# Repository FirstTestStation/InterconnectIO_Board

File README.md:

# FIRST STATION TEST Interconnect IO Board 600-1000-011

## Project Overview
This project involves the assembly of a custom **Interconnect IO Circuit Board (PCB)** designed to be part of the **First TestStation** project ([FTS](https://FirstTestSTation.github.io/FTS_Website/)). The primary goal of the Interconnect IO board is to provide an interface between instruments and the Unit Under Test (U.U.T).

Many resources, such as **bank relays**, **power relays**, **Digital IO** and **communication interfaces**, have been integrated into the Interconnect IO board. These resources reduce the need for external instruments and maximize the versatility of the interface, allowing for efficient testing and broader functionality.

### Design Tools
- [KiCad 7](https://www.kicad.org/download/) - Free software application used to design the PCB.
- [LibreOffice](https://www.libreoffice.org/download/download-libreoffice/) - Free Software application used to create assembly instructions and the Bill of Materials (BOM).
- [PicPick](https://picpick.app/en/) - Free application to capture and document image.

---
### Features
- **Easy Hand Assembly**: Designed with only through-hole components, making it easy to assemble by hand.
- **Socketed Active Components**: To facilitate easy replacement without unsoldering, most active components are mounted on sockets.
- **Cost-Effective Controller**: The low-cost and powerful **Raspberry Pi Pico Microcontroller** is used to interface with the user and control internal electronics.

## Assembly Instructions
   Follow the document [Assembly_Instructions](InterconnectIO_bd/pdf/InterconnectIO_Assembly_Instruction_680-1000.pdf) to complete the assembly of the board.

## Design Files
- [Gerber Files](InterconnectIO_bd/gerber_to_order/) – Gerber files for PCB fabrication, send zip file to manufacturer (JLCPCB is the one used by the project).
- [Assembly Schematic](InterconnectIO_bd/pdf/InterconnectIO_Assembly_diagram_670-1000.pdf) – Parts and value to help hand assemblies of components.
- [Electrical Schematic](InterconnectIO_bd/pdf/interconnectIO_schematic_640-1000.pdf) – Review the full electrical schematic diagram for reference.
- [Bill of Materials (BOM)](InterconnectIO_bd/pdf/BOM_InterconnectIO_Board_610-1000.pdf) – List of components required for assembly.

---

## License

This project is licensed under the terms of the [CERN Open Hardware License Version 2 - Weakly Reciprocal (CERN-OHL-W 2.0)](https://ohwr.org/cern_ohl_w_v2.txt).

See the [LICENSE](./LICENSE) file in this repository for more details.

---

## History
- **Version 1.0**: The initial version of the PCB (600-1010-010) has been assembled and tested. Wiring errors on the UART were identified and corrected manually using wires.
- **Version 1.1**: This version addresses all errors identified in Version 1.0. As of now, Version 1.1 has not yet been assembled or tested.
---

## Contact
For any issues or further questions, feel free to contact me at [daniellockhead@gmail.com] or open an issue on GitHub.

---

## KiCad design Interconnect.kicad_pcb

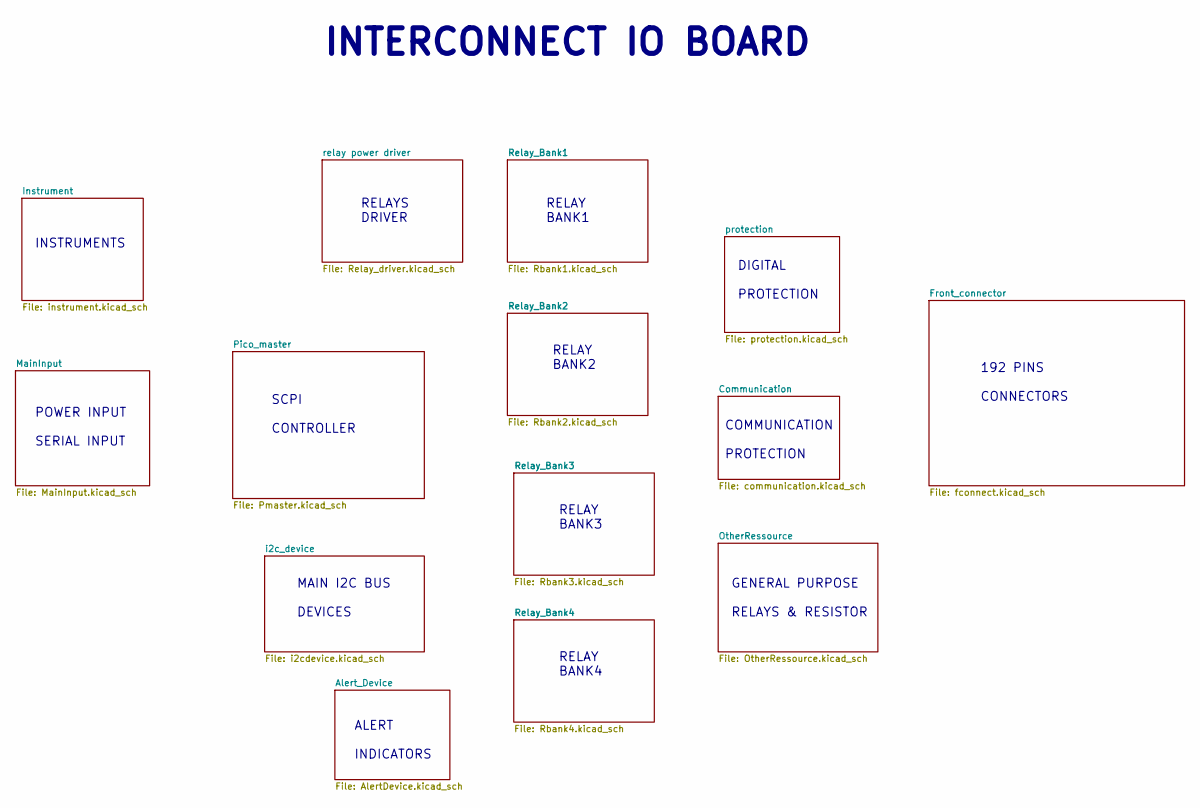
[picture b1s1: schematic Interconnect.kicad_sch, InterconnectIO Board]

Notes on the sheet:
ALERT INDICATORS
COMMUNICATION PROTECTION
SCPI CONTROLLER
RELAY BANK3
RELAYS DRIVER
INTERCONNECT IO BOARD
INSTRUMENTS
DIGITAL PROTECTION
GENERAL PURPOSE RELAYS & RESISTOR
192 PINS CONNECTORS
MAIN I2C BUS DEVICES
RELAY BANK2
RELAY BANK1
POWER INPUT SERIAL INPUT
RELAY BANK4

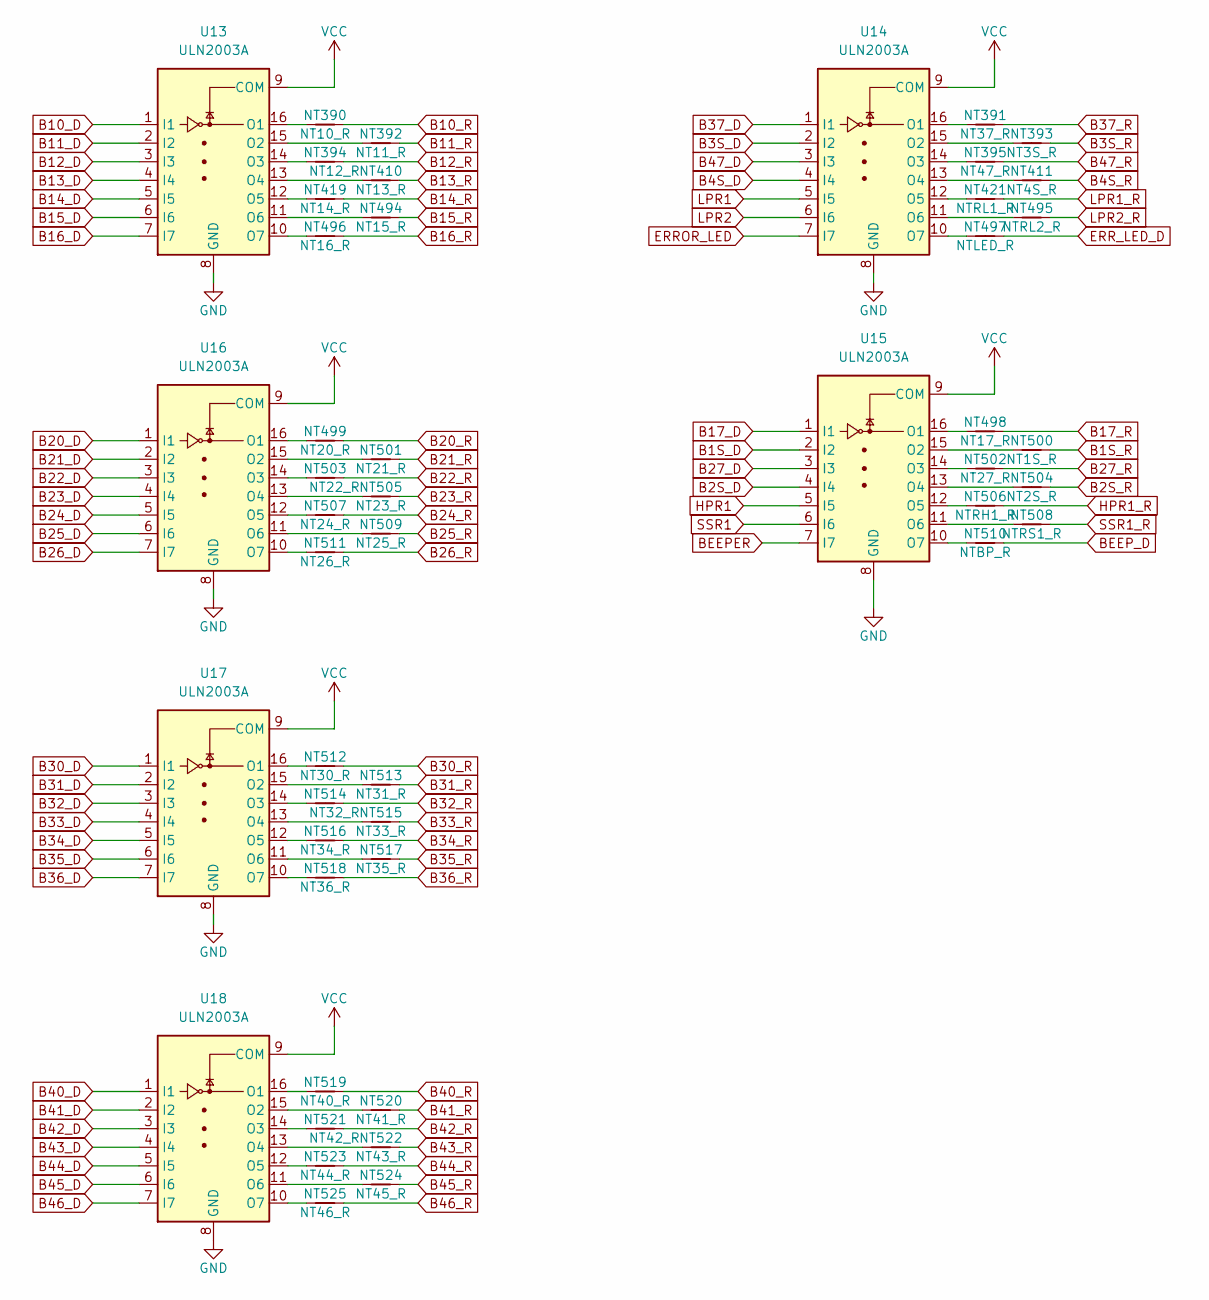
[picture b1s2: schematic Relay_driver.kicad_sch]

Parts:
NT390: NT10_R; NetTie-2_Front1.0mm
NT391: NT37_R; NetTie-2_Front1.0mm
NT392: NT11_R; NetTie-2_Front1.0mm
NT393: NT3S_R; NetTie-2_Front1.0mm
NT394: NT12_R; NetTie-2_Front1.0mm
NT395: NT47_R; NetTie-2_Front1.0mm
NT410: NT13_R; NetTie-2_Front1.0mm
NT411: NT4S_R; NetTie-2_Front1.0mm
NT419: NT14_R; NetTie-2_Front1.0mm
NT421: NTRL1_R; NetTie-2_Front1.0mm
NT494: NT15_R; NetTie-2_Front1.0mm
NT495: NTRL2_R; NetTie-2_Front1.0mm
NT496: NT16_R; NetTie-2_Front1.0mm
NT497: NTLED_R; NetTie-2_Front1.0mm
NT498: NT17_R; NetTie-2_Front1.0mm
NT499: NT20_R; NetTie-2_Front1.0mm
NT500: NT1S_R; NetTie-2_Front1.0mm
NT501: NT21_R; NetTie-2_Front1.0mm
NT502: NT27_R; NetTie-2_Front1.0mm
NT503: NT22_R; NetTie-2_Front1.0mm
NT504: NT2S_R; NetTie-2_Front1.0mm
NT505: NT23_R; NetTie-2_Front1.0mm
NT506: NTRH1_R; NetTie-2_Front1.0mm
NT507: NT24_R; NetTie-2_Front1.0mm
NT508: NTRS1_R; NetTie-2_Front1.0mm
NT509: NT25_R; NetTie-2_Front1.0mm
NT510: NTBP_R; NetTie-2_Front1.0mm
NT511: NT26_R; NetTie-2_Front1.0mm
NT512: NT30_R; NetTie-2_Front1.0mm
NT513: NT31_R; NetTie-2_Front1.0mm
NT514: NT32_R; NetTie-2_Front1.0mm
NT515: NT33_R; NetTie-2_Front1.0mm
NT516: NT34_R; NetTie-2_Front1.0mm
NT517: NT35_R; NetTie-2_Front1.0mm
NT518: NT36_R; NetTie-2_Front1.0mm
NT519: NT40_R; NetTie-2_Front1.0mm
NT520: NT41_R; NetTie-2_Front1.0mm
NT521: NT42_R; NetTie-2_Front1.0mm
NT522: NT43_R; NetTie-2_Front1.0mm
NT523: NT44_R; NetTie-2_Front1.0mm
NT524: NT45_R; NetTie-2_Front1.0mm
NT525: NT46_R; NetTie-2_Front1.0mm
U13, U14, U15, U16, U17, U18: ULN2003A; DIP-16_W7.62mm_LongPads

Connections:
B1S_D: U15.2 (I2); also elsewhere on the board
B1S_R: NT500.2; also elsewhere on the board
B2S_D: U15.4 (I4); also elsewhere on the board
B2S_R: NT504.2; also elsewhere on the board
B3S_D: U14.2 (I2); also elsewhere on the board
B3S_R: NT393.2; also elsewhere on the board
B4S_D: U14.4 (I4); also elsewhere on the board
B4S_R: NT411.2; also elsewhere on the board
B10_D: U13.1 (I1); also elsewhere on the board
B10_R: NT390.2; also elsewhere on the board
B11_D: U13.2 (I2); also elsewhere on the board
B11_R: NT392.2
B12_D: U13.3 (I3); also elsewhere on the board
B12_R: NT394.2; also elsewhere on the board
B13_D: U13.4 (I4); also elsewhere on the board
B13_R: NT410.2; also elsewhere on the board
B14_D: U13.5 (I5); also elsewhere on the board
B14_R: NT419.2; also elsewhere on the board
B15_D: U13.6 (I6); also elsewhere on the board
B15_R: NT494.2; also elsewhere on the board
B16_D: U13.7 (I7); also elsewhere on the board
B16_R: NT496.2; also elsewhere on the board
B17_D: U15.1 (I1); also elsewhere on the board
B17_R: NT498.2; also elsewhere on the board
B20_D: U16.1 (I1); also elsewhere on the board
B20_R: NT499.2; also elsewhere on the board
B21_D: U16.2 (I2); also elsewhere on the board
B21_R: NT501.2; also elsewhere on the board
B22_D: U16.3 (I3); also elsewhere on the board
B22_R: NT503.2; also elsewhere on the board
B23_D: U16.4 (I4); also elsewhere on the board
B23_R: NT505.2; also elsewhere on the board
B24_D: U16.5 (I5); also elsewhere on the board
B24_R: NT507.2; also elsewhere on the board
B25_D: U16.6 (I6); also elsewhere on the board
B25_R: NT509.2; also elsewhere on the board
B26_D: U16.7 (I7); also elsewhere on the board
B26_R: NT511.2; also elsewhere on the board
B27_D: U15.3 (I3); also elsewhere on the board
B27_R: NT502.2; also elsewhere on the board
B30_D: U17.1 (I1); also elsewhere on the board
B30_R: NT512.2; also elsewhere on the board
B31_D: U17.2 (I2); also elsewhere on the board
B31_R: NT513.2
B32_D: U17.3 (I3); also elsewhere on the board
B32_R: NT514.2; also elsewhere on the board
B33_D: U17.4 (I4); also elsewhere on the board
B33_R: NT515.2; also elsewhere on the board
B34_D: U17.5 (I5); also elsewhere on the board
B34_R: NT516.2; also elsewhere on the board
B35_D: U17.6 (I6); also elsewhere on the board
B35_R: NT517.2; also elsewhere on the board
B36_D: U17.7 (I7); also elsewhere on the board
B36_R: NT518.2; also elsewhere on the board
B37_D: U14.1 (I1); also elsewhere on the board
B37_R: NT391.2; also elsewhere on the board
B40_D: U18.1 (I1); also elsewhere on the board
B40_R: NT519.2; also elsewhere on the board
B41_D: U18.2 (I2); also elsewhere on the board
B41_R: NT520.2; also elsewhere on the board
B42_D: U18.3 (I3); also elsewhere on the board
B42_R: NT521.2; also elsewhere on the board
B43_D: U18.4 (I4); also elsewhere on the board
B43_R: NT522.2; also elsewhere on the board
B44_D: U18.5 (I5); also elsewhere on the board
B44_R: NT523.2; also elsewhere on the board
B45_D: U18.6 (I6); also elsewhere on the board
B45_R: NT524.2; also elsewhere on the board
B46_D: U18.7 (I7); also elsewhere on the board
B46_R: NT525.2; also elsewhere on the board
B47_D: U14.3 (I3); also elsewhere on the board
B47_R: NT395.2; also elsewhere on the board
BEEPER: U15.7 (I7); also elsewhere on the board
BEEP_D: NT510.2; also elsewhere on the board
ERROR_LED: U14.7 (I7); also elsewhere on the board
ERR_LED_D: NT497.2
GND: U13.8 (GND), U14.8 (GND), U15.8 (GND), U16.8 (GND), U17.8 (GND), U18.8 (GND); also elsewhere on the board
HPR1: U15.5 (I5); also elsewhere on the board
HPR1_R: NT506.2; also elsewhere on the board
LPR1: U14.5 (I5); also elsewhere on the board
LPR1_R: NT421.2; also elsewhere on the board
LPR2: U14.6 (I6); also elsewhere on the board
LPR2_R: NT495.2; also elsewhere on the board
unnamed: NT390.1, U13.16 (O1)
unnamed: NT391.1, U14.16 (O1)
unnamed: NT392.1, U13.15 (O2)
unnamed: NT393.1, U14.15 (O2)
unnamed: NT394.1, U13.14 (O3)
unnamed: NT395.1, U14.14 (O3)
unnamed: NT410.1, U13.13 (O4)
unnamed: NT411.1, U14.13 (O4)
unnamed: NT419.1, U13.12 (O5)
unnamed: NT421.1, U14.12 (O5)
unnamed: NT494.1, U13.11 (O6)
unnamed: NT495.1, U14.11 (O6)
unnamed: NT496.1, U13.10 (O7)
unnamed: NT497.1, U14.10 (O7)
unnamed: NT498.1, U15.16 (O1)
unnamed: NT499.1, U16.16 (O1)
unnamed: NT500.1, U15.15 (O2)
unnamed: NT501.1, U16.15 (O2)
unnamed: NT502.1, U15.14 (O3)
unnamed: NT503.1, U16.14 (O3)
unnamed: NT504.1, U15.13 (O4)
unnamed: NT505.1, U16.13 (O4)
unnamed: NT506.1, U15.12 (O5)
unnamed: NT507.1, U16.12 (O5)
unnamed: NT508.1, U15.11 (O6)
unnamed: NT509.1, U16.11 (O6)
unnamed: NT510.1, U15.10 (O7)
unnamed: NT511.1, U16.10 (O7)
unnamed: NT512.1, U17.16 (O1)
unnamed: NT513.1, U17.15 (O2)
unnamed: NT514.1, U17.14 (O3)
unnamed: NT515.1, U17.13 (O4)
unnamed: NT516.1, U17.12 (O5)
unnamed: NT517.1, U17.11 (O6)
unnamed: NT518.1, U17.10 (O7)
unnamed: NT519.1, U18.16 (O1)
unnamed: NT520.1, U18.15 (O2)
unnamed: NT521.1, U18.14 (O3)
unnamed: NT522.1, U18.13 (O4)
unnamed: NT523.1, U18.12 (O5)
unnamed: NT524.1, U18.11 (O6)
unnamed: NT525.1, U18.10 (O7)
PWR_5V: U13.9 (COM), U14.9 (COM), U15.9 (COM), U16.9 (COM), U17.9 (COM), U18.9 (COM); also elsewhere on the board
SSR1: U15.6 (I6); also elsewhere on the board
SSR1_R: NT508.2; also elsewhere on the board

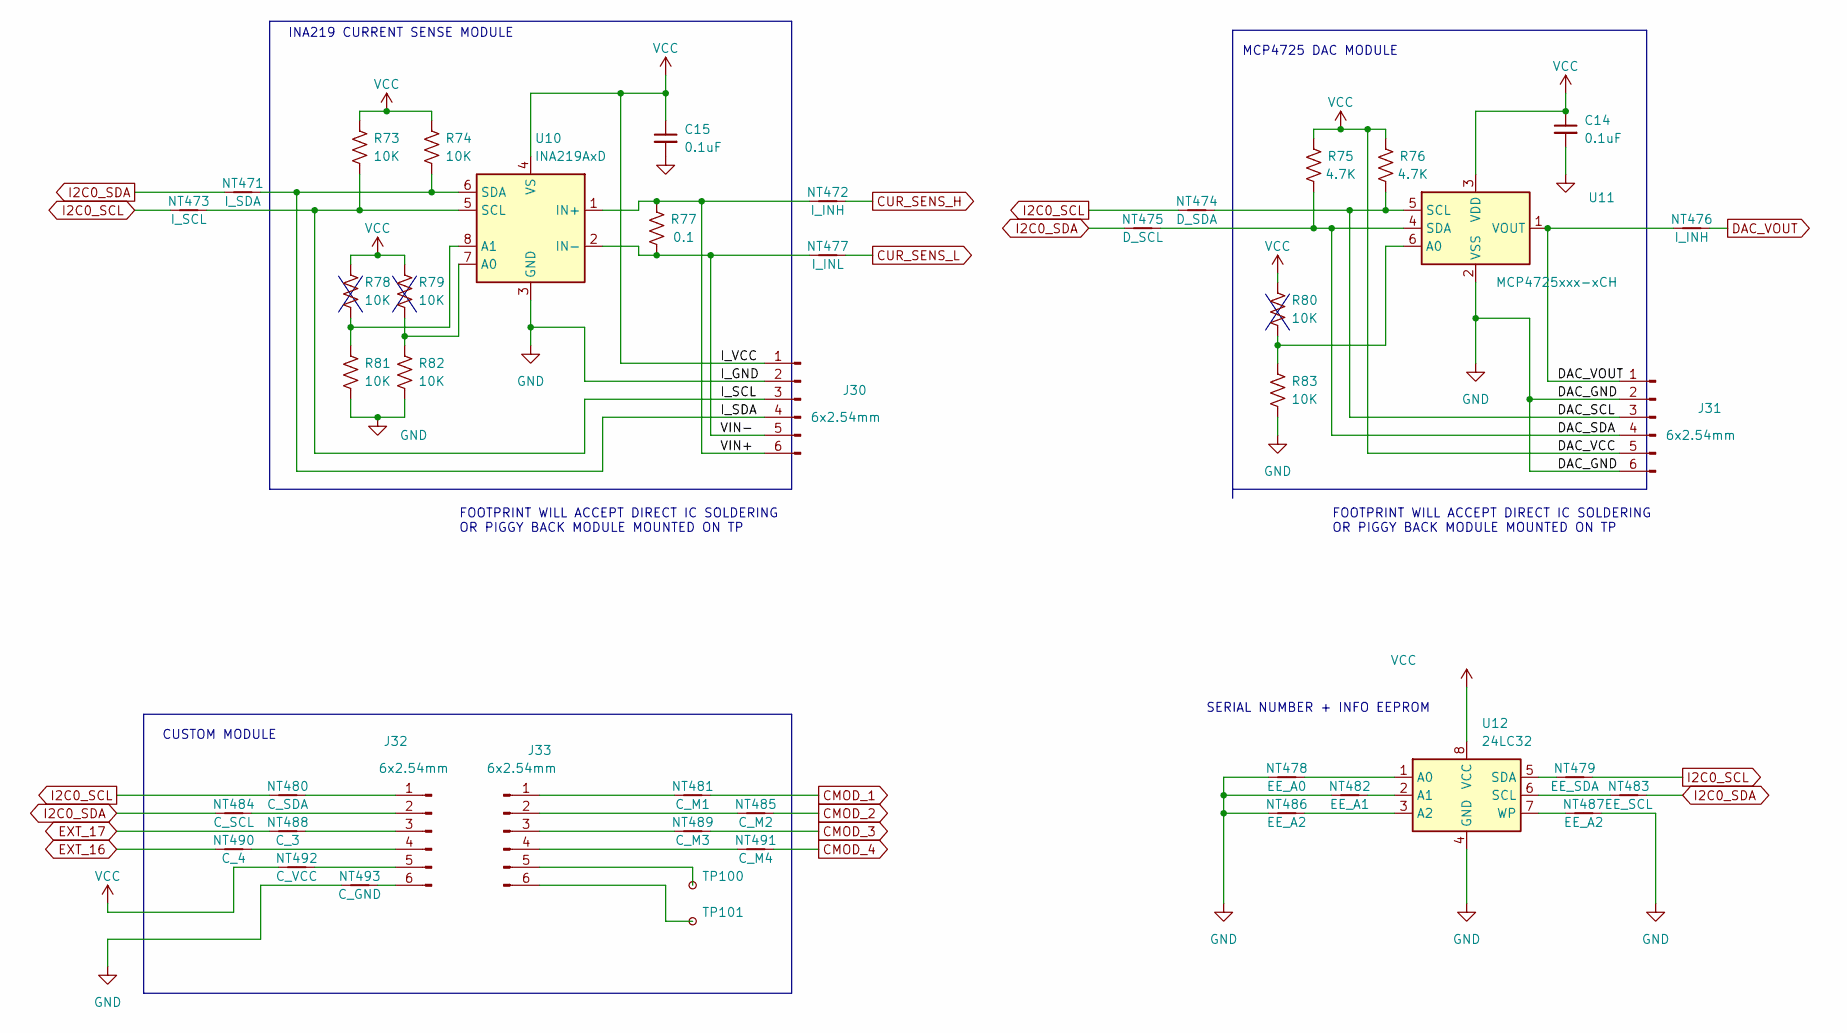
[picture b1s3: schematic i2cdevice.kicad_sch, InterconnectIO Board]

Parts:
C14: 0.1uF; C_0603_1608Metric_Pad1.08x0.95mm_HandSolder
C15: 0.1uF; C_0805_2012Metric_Pad1.18x1.45mm_HandSolder
J30, J31, J32, J33: 6x2.54mm; PinHeader_1x06_P2.54mm_Vertical
NT471: I_SDA; NetTie-2_Front1.0mm
NT472, NT476: I_INH; NetTie-2_Front1.0mm
NT473: I_SCL; NetTie-2_Front1.0mm
NT474: D_SDA; NetTie-2_Front1.0mm
NT475: D_SCL; NetTie-2_Front1.0mm
NT477: I_INL; NetTie-2_Front1.0mm
NT478: EE_A0; NetTie-2_Front1.0mm
NT479: EE_SDA; NetTie-2_Front1.0mm
NT480: C_SDA; NetTie-2_Front1.0mm
NT481: C_M1; NetTie-2_Front1.0mm
NT482: EE_A1; NetTie-2_Front1.0mm
NT483: EE_SCL; NetTie-2_Front1.0mm
NT484: C_SCL; NetTie-2_Front1.0mm
NT485: C_M2; NetTie-2_Front1.0mm
NT486, NT487: EE_A2; NetTie-2_Front1.0mm
NT488: C_3; NetTie-2_Front1.0mm
NT489: C_M3; NetTie-2_Front1.0mm
NT490: C_4; NetTie-2_Front1.0mm
NT491: C_M4; NetTie-2_Front1.0mm
NT492: C_VCC; NetTie-2_Front1.0mm
NT493: C_GND; NetTie-2_Front1.0mm
R73, R74, R78, R79, R80, R81, R82: 10K; R_0805_2012Metric_Pad1.20x1.40mm_HandSolder
R75, R76: 4.7K; R_0603_1608Metric_Pad0.98x0.95mm_HandSolder
R77: 0.1; R_2512_6332Metric_Pad1.40x3.35mm_HandSolder
R83: 10K; R_0603_1608Metric_Pad0.98x0.95mm_HandSolder
TP100, TP101: TestPoint_Small; Pin_D0.9mm_L10.0mm_W2.4mm_FlatFork
U10: INA219AxD; SOT-23-8
U11: MCP4725xxx-xCH; SOT-23-6
U12: 24LC32; DIP-8_W7.62mm

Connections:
/i2c_device/DAC_SCL: J31.3, NT474.2, R76.1, U11.5 (SCL)
/i2c_device/DAC_SDA: J31.4, NT475.2, R75.1, U11.4 (SDA)
/i2c_device/I_SCL: J30.3, NT473.2, R73.1, U10.5 (SCL)
/i2c_device/I_SDA: J30.4, NT471.2, R74.1, U10.6 (SDA)
/i2c_device/VIN+: J30.6, NT472.2, R77.2, U10.1 (IN+)
/i2c_device/VIN-: J30.5, NT477.2, R77.1, U10.2 (IN-)
CMOD_1: NT481.2; also elsewhere on the board
CMOD_2: NT485.2; also elsewhere on the board
CMOD_3: NT489.2; also elsewhere on the board
CMOD_4: NT491.2; also elsewhere on the board
CUR_SENS_H: NT472.1; also elsewhere on the board
CUR_SENS_L: NT477.1; also elsewhere on the board
DAC_VOUT: J31.1, NT476.1, NT476.2, U11.1 (VOUT); also elsewhere on the board
EXT_16: NT490.1; also elsewhere on the board
EXT_17: NT488.1; also elsewhere on the board
GND: C14.2, C15.2, J30.2, J31.2, J31.6, NT478.1, NT482.1, NT486.1, NT487.1, NT493.1, R81.1, R82.1, R83.1, U10.3 (GND), U11.2 (VSS), U12.4 (GND); also elsewhere on the board
I2C0_SCL: NT473.1, NT474.1, NT479.1, NT480.1; also elsewhere on the board
I2C0_SDA: NT471.1, NT475.1, NT483.1, NT484.1; also elsewhere on the board
unnamed: J32.1, NT480.2
unnamed: J32.2, NT484.2
unnamed: J32.3, NT488.2
unnamed: J32.4, NT490.2
unnamed: J32.5, NT492.2
unnamed: J32.6, NT493.2
unnamed: J33.1, NT481.1
unnamed: J33.2, NT485.1
unnamed: J33.3, NT489.1
unnamed: J33.4, NT491.1
unnamed: J33.5, TP100.1
unnamed: J33.6, TP101.1
unnamed: NT478.2, U12.1 (A0)
unnamed: NT479.2, U12.5 (SDA)
unnamed: NT482.2, U12.2 (A1)
unnamed: NT483.2, U12.6 (SCL)
unnamed: NT486.2, U12.3 (A2)
unnamed: NT487.2, U12.7 (WP)
unnamed: R78.1, R81.2, U10.8 (A1)
unnamed: R79.1, R82.2, U10.7 (A0)
unnamed: R80.1, R83.2, U11.6 (A0)
PWR_5V: C14.1, C15.1, J30.1, J31.5, NT492.1, R73.2, R74.2, R75.2, R76.2, R78.2, R79.2, R80.2, U10.4 (VS), U11.3 (VDD), U12.8 (VCC); also elsewhere on the board

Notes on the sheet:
INA219 CURRENT SENSE MODULE
FOOTPRINT WILL ACCEPT DIRECT IC SOLDERING OR PIGGY BACK MODULE MOUNTED ON TP
MCP4725 DAC MODULE
CUSTOM MODULE
SERIAL NUMBER + INFO EEPROM

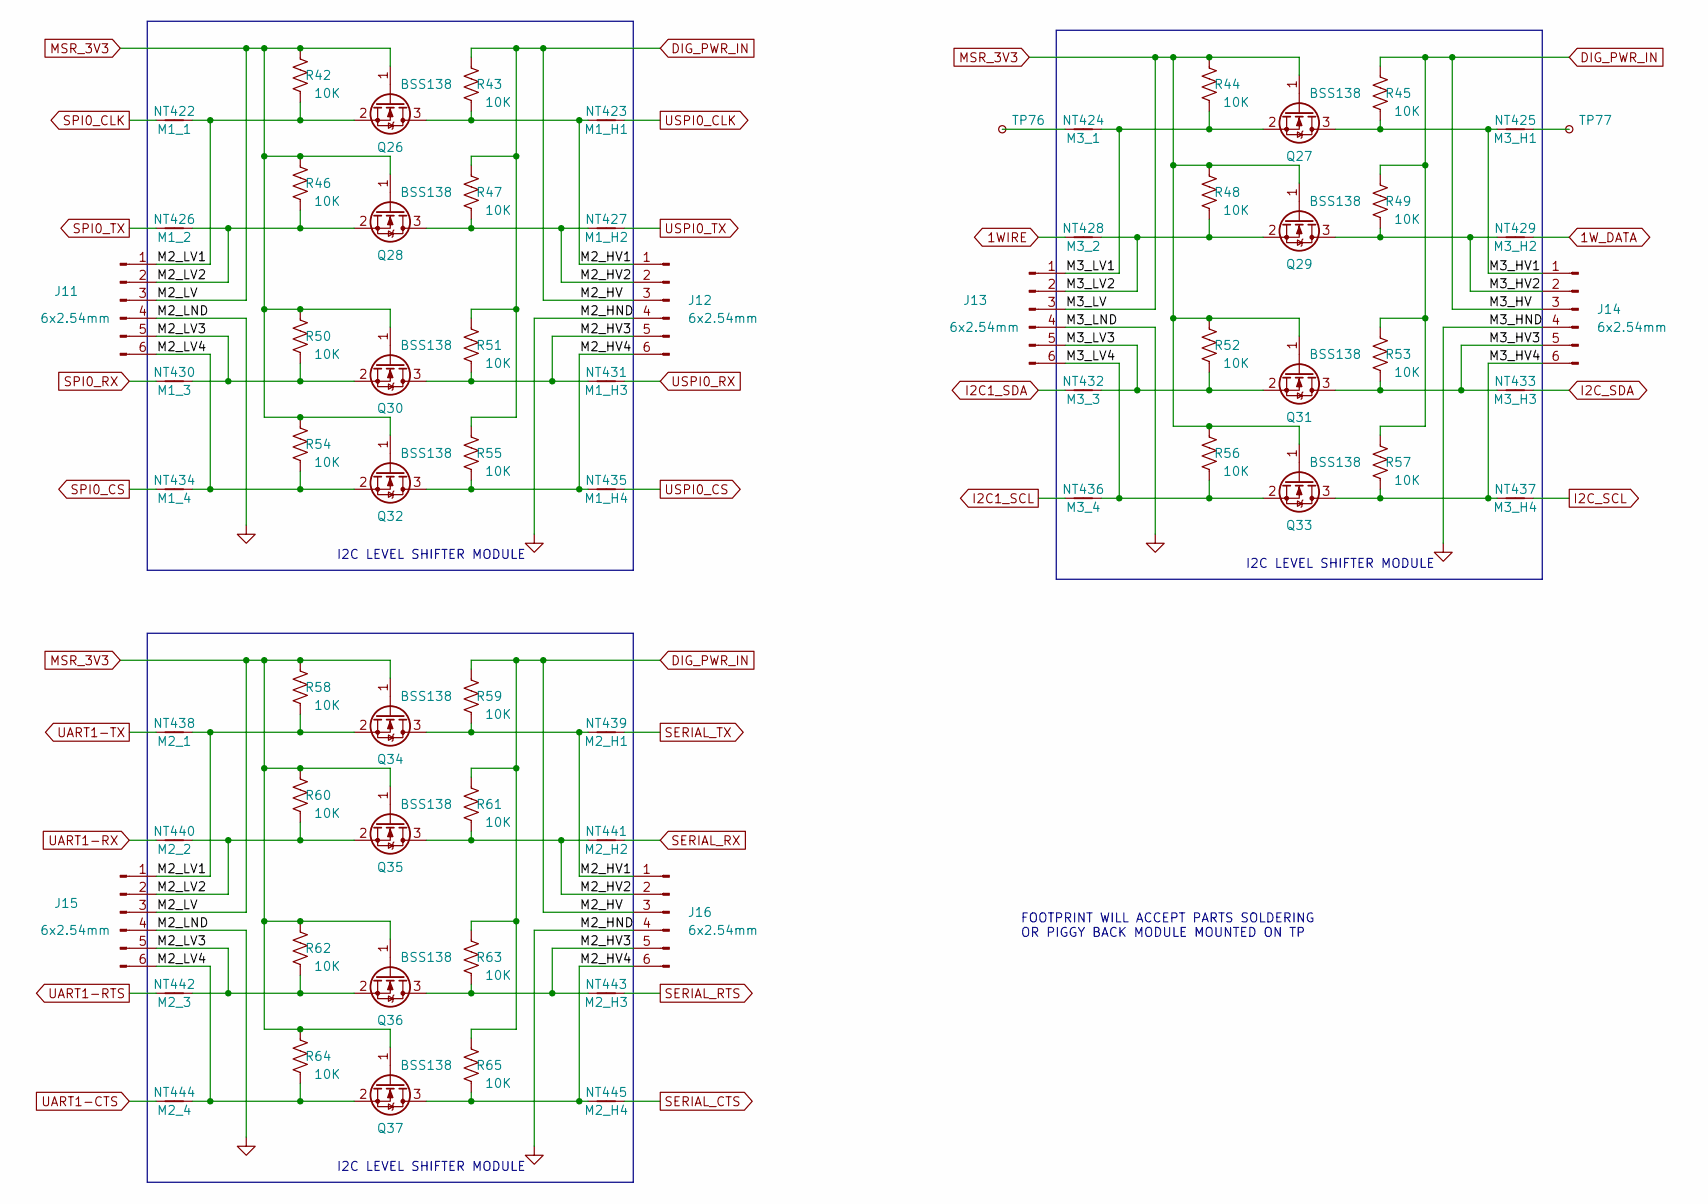
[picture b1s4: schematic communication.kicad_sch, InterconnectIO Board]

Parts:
J11, J12, J13, J14, J15, J16: 6x2.54mm; PinHeader_1x06_P2.54mm_Vertical
NT422: M1_1; NetTie-2_Front1.0mm
NT423: M1_H1; NetTie-2_Front1.0mm
NT424: M3_1; NetTie-2_Front1.0mm
NT425: M3_H1; NetTie-2_Front1.0mm
NT426: M1_2; NetTie-2_Front1.0mm
NT427: M1_H2; NetTie-2_Front1.0mm
NT428: M3_2; NetTie-2_Front1.0mm
NT429: M3_H2; NetTie-2_Front1.0mm
NT430: M1_3; NetTie-2_Front1.0mm
NT431: M1_H3; NetTie-2_Front1.0mm
NT432: M3_3; NetTie-2_Front1.0mm
NT433: M3_H3; NetTie-2_Front1.0mm
NT434: M1_4; NetTie-2_Front1.0mm
NT435: M1_H4; NetTie-2_Front1.0mm
NT436: M3_4; NetTie-2_Front1.0mm
NT437: M3_H4; NetTie-2_Front1.0mm
NT438: M2_1; NetTie-2_Front1.0mm
NT439: M2_H1; NetTie-2_Front1.0mm
NT440: M2_2; NetTie-2_Front1.0mm
NT441: M2_H2; NetTie-2_Front1.0mm
NT442: M2_3; NetTie-2_Front1.0mm
NT443: M2_H3; NetTie-2_Front1.0mm
NT444: M2_4; NetTie-2_Front1.0mm
NT445: M2_H4; NetTie-2_Front1.0mm
Q26, Q27, Q28, Q29, Q30, Q31, Q32, Q33, Q34, Q35, Q36, Q37: BSS138; SOT-23W
R42, R43, R44, R45, R46, R47, R48, R49, R50, R51, R52, R53, R54, R55, R56, R57, R58, R59, R60, R61, R62, R63, R64, R65: 10K; R_0603_1608Metric
TP76, TP77: TestPoint_Small; Pin_D0.9mm_L10.0mm_W2.4mm_FlatFork

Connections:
1WIRE: NT428.1; also elsewhere on the board
1W_DATA: NT429.1; also elsewhere on the board
/Communication/M2_HV1: J12.1, J16.1, NT423.2, NT439.2, Q26.3 (D), Q34.3 (D), R43.1, R59.1
/Communication/M2_HV2: J12.2, J16.2, NT427.2, NT441.2, Q28.3 (D), Q35.3 (D), R47.1, R61.1
/Communication/M2_HV3: J12.5, J16.5, NT431.2, NT443.2, Q30.3 (D), Q36.3 (D), R51.1, R63.1
/Communication/M2_HV4: J12.6, J16.6, NT435.2, NT445.2, Q32.3 (D), Q37.3 (D), R55.1, R65.1
/Communication/M2_LV1: J11.1, J15.1, NT422.2, NT438.2, Q26.2 (S), Q34.2 (S), R42.1, R58.1
/Communication/M2_LV2: J11.2, J15.2, NT426.2, NT440.2, Q28.2 (S), Q35.2 (S), R46.1, R60.1
/Communication/M2_LV3: J11.5, J15.5, NT430.2, NT442.2, Q30.2 (S), Q36.2 (S), R50.1, R62.1
/Communication/M2_LV4: J11.6, J15.6, NT434.2, NT444.2, Q32.2 (S), Q37.2 (S), R54.1, R64.1
/Communication/M3_HV1: J14.1, NT425.2, Q27.3 (D), R45.1
/Communication/M3_HV2: J14.2, NT429.2, Q29.3 (D), R49.1
/Communication/M3_HV3: J14.5, NT433.2, Q31.3 (D), R53.1
/Communication/M3_HV4: J14.6, NT437.2, Q33.3 (D), R57.1
/Communication/M3_LV1: J13.1, NT424.2, Q27.2 (S), R44.1
/Communication/M3_LV2: J13.2, NT428.2, Q29.2 (S), R48.1
/Communication/M3_LV3: J13.5, NT432.2, Q31.2 (S), R52.1
/Communication/M3_LV4: J13.6, NT436.2, Q33.2 (S), R56.1
DIG_PWR_IN: J12.3, J14.3, J16.3, R43.2, R45.2, R47.2, R49.2, R51.2, R53.2, R55.2, R57.2, R59.2, R61.2, R63.2, R65.2; also elsewhere on the board
GND: J11.4, J12.4, J13.4, J14.4, J15.4, J16.4; also elsewhere on the board
I2C1_SCL: NT436.1; also elsewhere on the board
I2C1_SDA: NT432.1; also elsewhere on the board
I2C_SCL: NT437.1; also elsewhere on the board
I2C_SDA: NT433.1; also elsewhere on the board
MSR_3V3: J11.3, J13.3, J15.3, Q26.1 (G), Q27.1 (G), Q28.1 (G), Q29.1 (G), Q30.1 (G), Q31.1 (G), Q32.1 (G), Q33.1 (G), Q34.1 (G), Q35.1 (G), Q36.1 (G), Q37.1 (G), R42.2, R44.2, R46.2, R48.2, R50.2, R52.2, R54.2, R56.2, R58.2, R60.2, R62.2, R64.2; also elsewhere on the board
unnamed: NT424.1, TP76.1
unnamed: NT425.1, TP77.1
SERIAL_CTS: NT445.1; also elsewhere on the board
SERIAL_RTS: NT443.1; also elsewhere on the board
SERIAL_RX: NT441.1; also elsewhere on the board
SERIAL_TX: NT439.1; also elsewhere on the board
SPI0_CLK: NT422.1; also elsewhere on the board
SPI0_CS: NT434.1; also elsewhere on the board
SPI0_RX: NT430.1; also elsewhere on the board
SPI0_TX: NT426.1; also elsewhere on the board
UART1-CTS: NT444.1; also elsewhere on the board
UART1-RTS: NT442.1; also elsewhere on the board
UART1-RX: NT440.1; also elsewhere on the board
UART1-TX: NT438.1; also elsewhere on the board
USPI0_CLK: NT423.1; also elsewhere on the board
USPI0_CS: NT435.1; also elsewhere on the board
USPI0_RX: NT431.1; also elsewhere on the board
USPI0_TX: NT427.1; also elsewhere on the board

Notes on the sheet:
FOOTPRINT WILL ACCEPT PARTS SOLDERING OR PIGGY BACK MODULE MOUNTED ON TP
I2C LEVEL SHIFTER MODULE

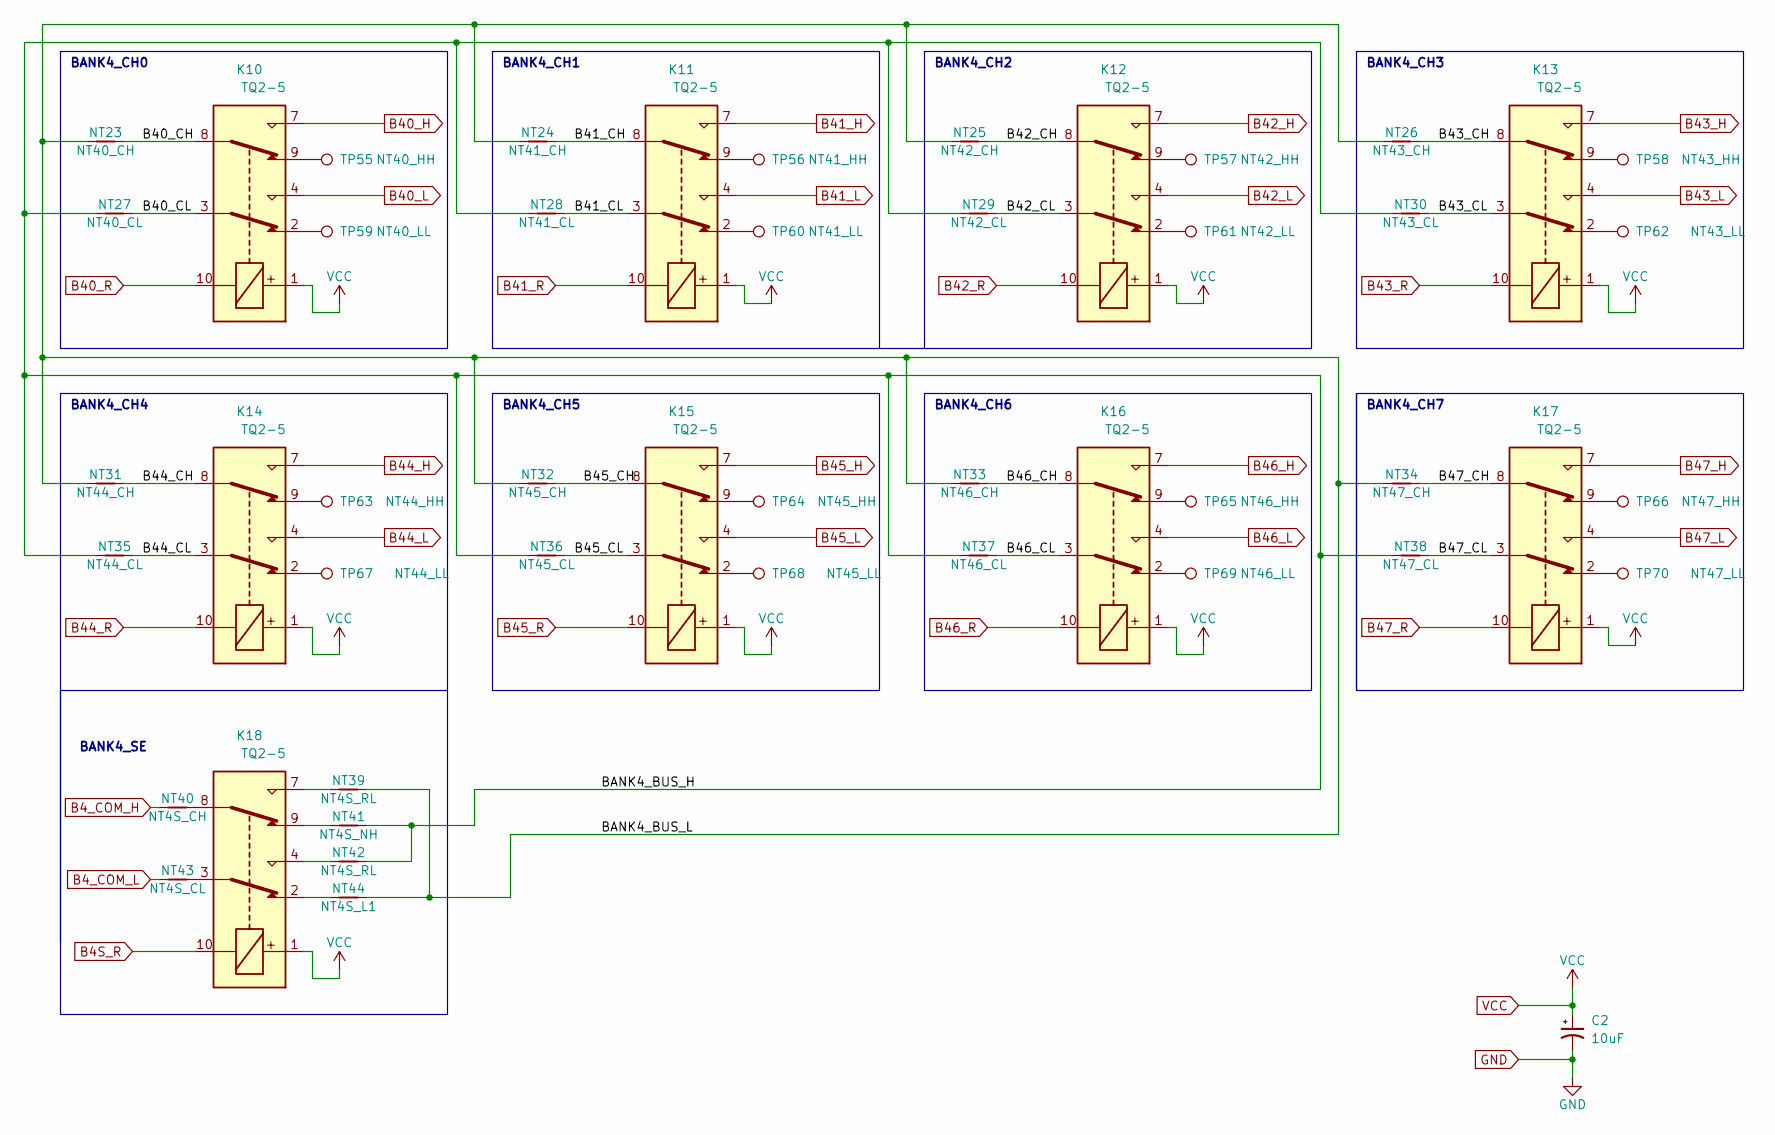
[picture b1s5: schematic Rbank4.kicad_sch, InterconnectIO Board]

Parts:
C2: 10uF; CP_Radial_D4.0mm_P1.50mm
K10, K11, K12, K13, K14, K15, K16, K17, K18: TQ2-5; Relay_DPDT_FRT5
NT23: NT40_CH; NetTie-2_Front1.0mm
NT24: NT41_CH; NetTie-2_Front1.0mm
NT25: NT42_CH; NetTie-2_Front1.0mm
NT26: NT43_CH; NetTie-2_Front1.0mm
NT27: NT40_CL; NetTie-2_Front1.0mm
NT28: NT41_CL; NetTie-2_Front1.0mm
NT29: NT42_CL; NetTie-2_Front1.0mm
NT30: NT43_CL; NetTie-2_Front1.0mm
NT31: NT44_CH; NetTie-2_Front1.0mm
NT32: NT45_CH; NetTie-2_Front1.0mm
NT33: NT46_CH; NetTie-2_Front1.0mm
NT34: NT47_CH; NetTie-2_Front1.0mm
NT35: NT44_CL; NetTie-2_Front1.0mm
NT36: NT45_CL; NetTie-2_Front1.0mm
NT37: NT46_CL; NetTie-2_Front1.0mm
NT38: NT47_CL; NetTie-2_Front1.0mm
NT39, NT42: NT4S_RL; NetTie-2_Front1.0mm
NT40: NT4S_CH; NetTie-2_Front1.0mm
NT41: NT4S_NH; NetTie-2_Front1.0mm
NT43: NT4S_CL; NetTie-2_Front1.0mm
NT44: NT4S_L1; NetTie-2_Front1.0mm
TP55: NT40_HH; Pin_D0.9mm_L10.0mm_W2.4mm_FlatFork
TP56: NT41_HH; Pin_D0.9mm_L10.0mm_W2.4mm_FlatFork
TP57: NT42_HH; Pin_D0.9mm_L10.0mm_W2.4mm_FlatFork
TP58: NT43_HH; Pin_D0.9mm_L10.0mm_W2.4mm_FlatFork
TP59: NT40_LL; Pin_D0.9mm_L10.0mm_W2.4mm_FlatFork
TP60: NT41_LL; Pin_D0.9mm_L10.0mm_W2.4mm_FlatFork
TP61: NT42_LL; Pin_D0.9mm_L10.0mm_W2.4mm_FlatFork
TP62: NT43_LL; Pin_D0.9mm_L10.0mm_W2.4mm_FlatFork
TP63: NT44_HH; Pin_D0.9mm_L10.0mm_W2.4mm_FlatFork
TP64: NT45_HH; Pin_D0.9mm_L10.0mm_W2.4mm_FlatFork
TP65: NT46_HH; Pin_D0.9mm_L10.0mm_W2.4mm_FlatFork
TP66: NT47_HH; Pin_D0.9mm_L10.0mm_W2.4mm_FlatFork
TP67: NT44_LL; Pin_D0.9mm_L10.0mm_W2.4mm_FlatFork
TP68: NT45_LL; Pin_D0.9mm_L10.0mm_W2.4mm_FlatFork
TP69: NT46_LL; Pin_D0.9mm_L10.0mm_W2.4mm_FlatFork
TP70: NT47_LL; Pin_D0.9mm_L10.0mm_W2.4mm_FlatFork

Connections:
/Relay_Bank4/B40_CH: K10.8, NT23.2
/Relay_Bank4/B40_CL: K10.3, NT27.2
/Relay_Bank4/B41_CH: K11.8, NT24.2
/Relay_Bank4/B41_CL: K11.3, NT28.2
/Relay_Bank4/B42_CH: K12.8, NT25.2
/Relay_Bank4/B42_CL: K12.3, NT29.2
/Relay_Bank4/B43_CH: K13.8, NT26.2
/Relay_Bank4/B43_CL: K13.3, NT30.2
/Relay_Bank4/B44_CH: K14.8, NT31.2
/Relay_Bank4/B44_CL: K14.3, NT35.2
/Relay_Bank4/B45_CH: K15.8, NT32.2
/Relay_Bank4/B45_CL: K15.3, NT36.2
/Relay_Bank4/B46_CH: K16.8, NT33.2
/Relay_Bank4/B46_CL: K16.3, NT37.2
/Relay_Bank4/B47_CH: K17.8, NT34.2
/Relay_Bank4/B47_CL: K17.3, NT38.2
/Relay_Bank4/BANK4_BUS_H: NT27.1, NT28.1, NT29.1, NT30.1, NT35.1, NT36.1, NT37.1, NT38.1, NT41.2, NT42.2
/Relay_Bank4/BANK4_BUS_L: NT23.1, NT24.1, NT25.1, NT26.1, NT31.1, NT32.1, NT33.1, NT34.1, NT39.2, NT44.2
B4S_R: K18.10; also elsewhere on the board
B4_COM_H: NT40.1; also elsewhere on the board
B4_COM_L: NT43.1; also elsewhere on the board
B40_H: K10.7; also elsewhere on the board
B40_L: K10.4; also elsewhere on the board
B40_R: K10.10; also elsewhere on the board
B41_H: K11.7; also elsewhere on the board
B41_L: K11.4; also elsewhere on the board
B41_R: K11.10; also elsewhere on the board
B42_H: K12.7; also elsewhere on the board
B42_L: K12.4; also elsewhere on the board
B42_R: K12.10; also elsewhere on the board
B43_H: K13.7; also elsewhere on the board
B43_L: K13.4; also elsewhere on the board
B43_R: K13.10; also elsewhere on the board
B44_H: K14.7; also elsewhere on the board
B44_L: K14.4; also elsewhere on the board
B44_R: K14.10; also elsewhere on the board
B45_H: K15.7; also elsewhere on the board
B45_L: K15.4; also elsewhere on the board
B45_R: K15.10; also elsewhere on the board
B46_H: K16.7; also elsewhere on the board
B46_L: K16.4; also elsewhere on the board
B46_R: K16.10; also elsewhere on the board
B47_H: K17.7; also elsewhere on the board
B47_L: K17.4; also elsewhere on the board
B47_R: K17.10; also elsewhere on the board
GND: C2.2; also elsewhere on the board
unnamed: K10.2, TP59.1
unnamed: K10.9, TP55.1
unnamed: K11.2, TP60.1
unnamed: K11.9, TP56.1
unnamed: K12.2, TP61.1
unnamed: K12.9, TP57.1
unnamed: K13.2, TP62.1
unnamed: K13.9, TP58.1
unnamed: K14.2, TP67.1
unnamed: K14.9, TP63.1
unnamed: K15.2, TP68.1
unnamed: K15.9, TP64.1
unnamed: K16.2, TP69.1
unnamed: K16.9, TP65.1
unnamed: K17.2, TP70.1
unnamed: K17.9, TP66.1
unnamed: K18.2, NT44.1
unnamed: K18.3, NT43.2
unnamed: K18.4, NT42.1
unnamed: K18.7, NT39.1
unnamed: K18.8, NT40.2
unnamed: K18.9, NT41.1
PWR_5V: C2.1, K10.1, K11.1, K12.1, K13.1, K14.1, K15.1, K16.1, K17.1, K18.1; also elsewhere on the board

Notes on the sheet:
BANK4_CH4
BANK4_CH7
BANK4_CH2
BANK4_SE
BANK4_CH3
BANK4_CH6
BANK4_CH1
BANK4_CH0
BANK4_CH5

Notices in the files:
InterconnectIO_bd/Interconnect.kicad_sch:
Copyright CERN 2020.
This source describes Open Hardware and is licensed under the CERN-OHLW v2
using it under the terms of the CERN-OHL-W v2 (https:/cern.ch/cern-ohl).
